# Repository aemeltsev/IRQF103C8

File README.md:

License
-------

IRQF103C8 schematic files and documentations are distributed under 
Creative Commons Attribution 4.0 International License.

Overview
--------
Using STM32 microcontroller for rapid prototyping.

![PCB image][IRQF103C8revC_BRD]

[IRQF103C8revC_BRD]: https://github.com/aemeltsev/IRQF103C8/blob/master/Documents/IRQF103C8revC_BRD.png

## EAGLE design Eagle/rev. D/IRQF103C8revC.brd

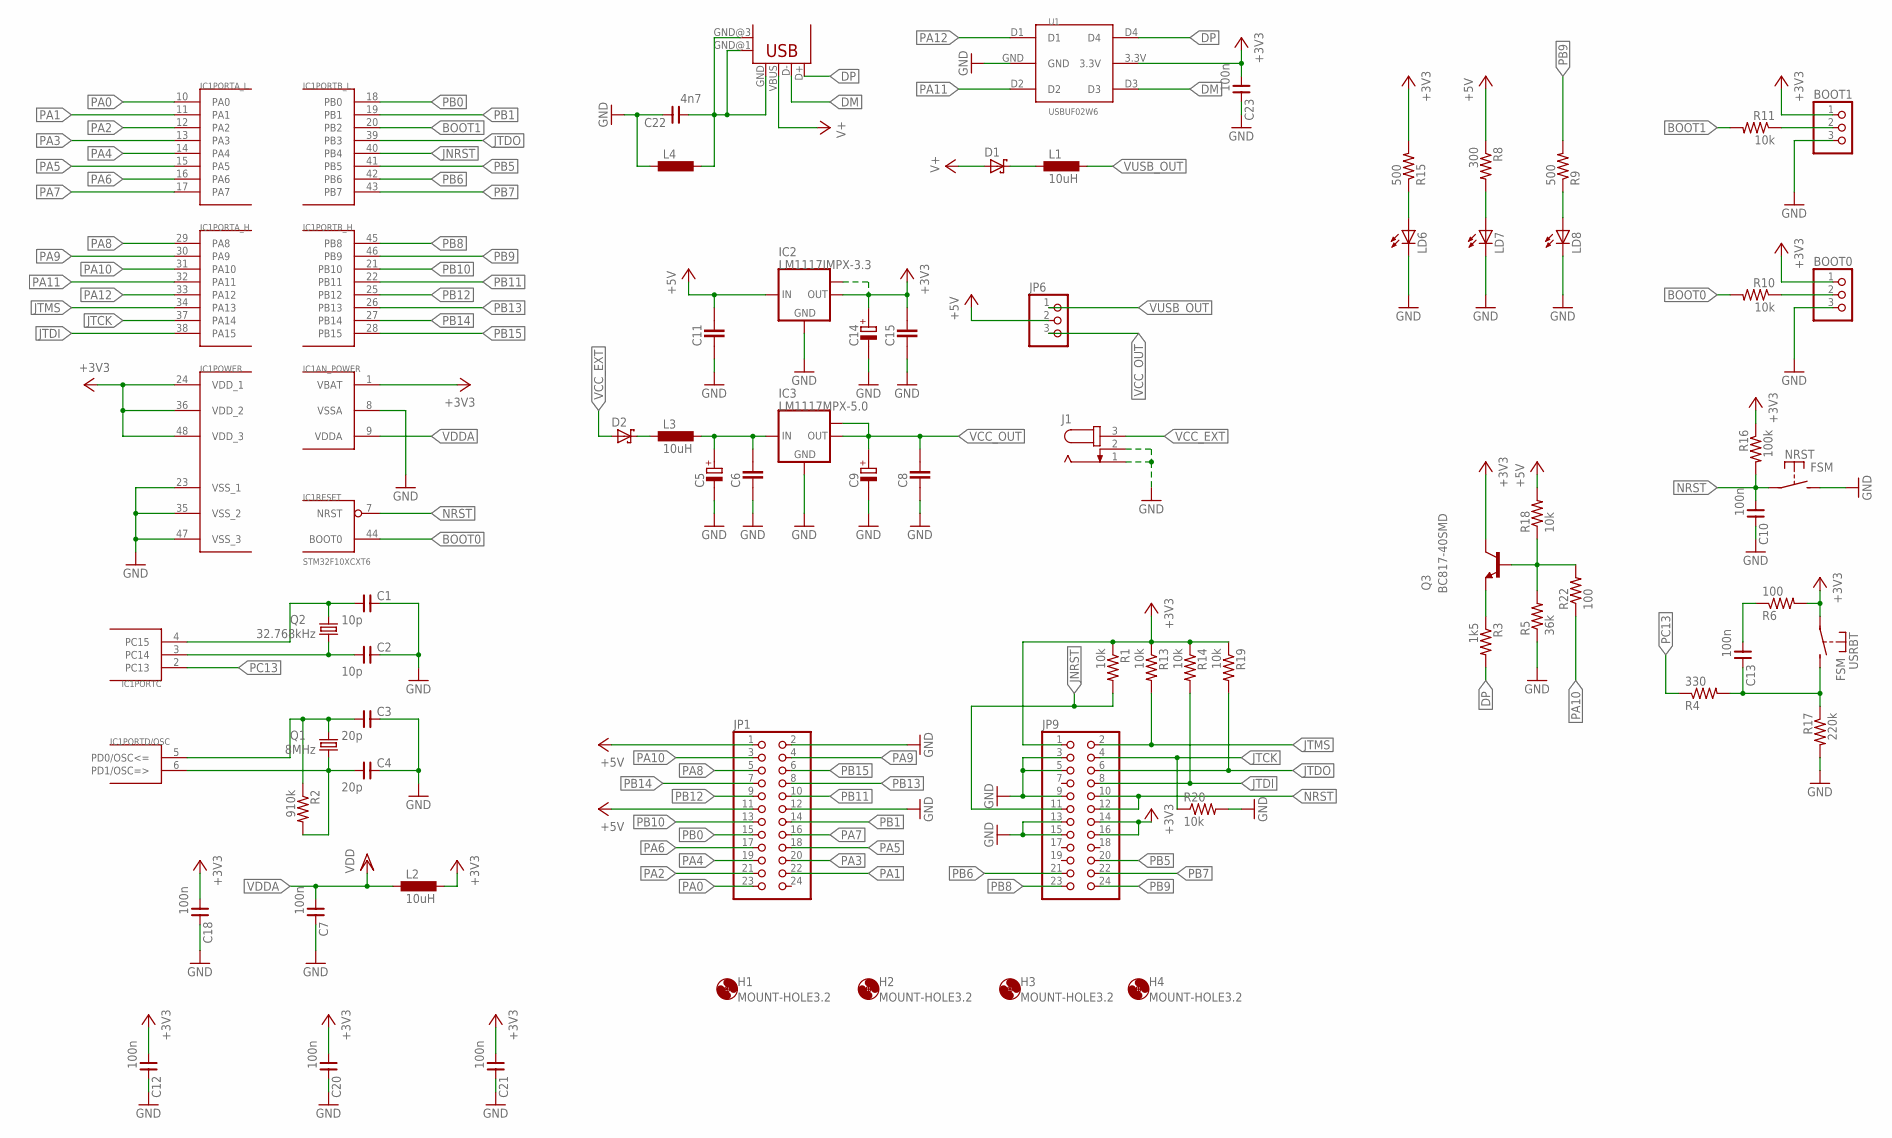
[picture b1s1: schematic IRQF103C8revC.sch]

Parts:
BOOT0, BOOT1: PINHD-1X3; 1X03
C1, C2: 10p; 0805
C3, C4: 20p; 0805
C5: POLARISED_CASE_B; CAPAE430X540N
C6, C8, C15: CAPACITOR_0805; CAPC2012X145AN
C7, C10, C12, C13, C18, C20, C21, C23: 100n; 0805
C9: POLARISED_CASE_D; CAPAE660X540N
C11: CAPACITOR_1206; CAPC3215X168N
C14: POLARISED_CASE_C; CAPAE530X540N
C22: 4n7; 0805
D1, D2: SCHOTTKY_SMA; DIOM5326X292N
H1, H2, H3, H4: MOUNT-HOLE3.2; 3,2
IC1: STM32F10XCXT6; TQFP48
IC2: LM1117IMPX-3.3; SOT223
IC3: LM1117MPX-5.0; SOT223
J1: JACK-PLUG1; SPC4078
JP1, JP9: PINHD-2X12; 2X12
JP6: PINHD-1X3; 1X03
L1, L2, L3: 10uH; INDC1608X95N
L4: INDUCTOR_0603; INDC1608X95N
LD6, LD7, LD8: LEDCHIPLED_0805; CHIPLED_0805
NRST: FSM
Q1: 8MHz; HC49/S
Q2: 32.768kHz; TC26H
Q3: BC817-40SMD; SOT23-BEC
R1, R10, R11, R13, R14, R18, R19, R20: 10k; M0805
R2: 910k; M0805
R3: 1k5; M0805
R4: 330; M0805
R5: 36k; M0805
R6, R22: 100; M0805
R8: 300; M0805
R9, R15: 500; M0805
R16: 100k; M0805
R17: 220k; M0805
U1: USBUF02W6; SOT23-6L
USB1: USB-MB-S
USRBT: FSM

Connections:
+3V3: BOOT0.1, BOOT1.1, C12.1, C14.+, C15.2, C18.1, C20.1, C21.1, C23.1, IC1.1 (VBAT), IC1.24 (VDD_1), IC1.36 (VDD_2), IC1.48 (VDD_3), IC2.2 (OUT), IC2.TAB (OUT1), JP9.1, JP9.14, JP9.16, L2.2, Q3.C, R1.1, R6.2, R13.1, R14.1, R15.2, R16.1, R19.1, U1.3.3V, USRBT.P$1
+5V: C11.2, IC2.3 (IN), JP1.1, JP1.11, JP6.2, R8.1, R18.2
BOOT0: IC1.44 (BOOT0), R10.2
BOOT1: IC1.20 (PB2), R11.2
DM: U1.D3, USB1.D-
DP: R3.2, U1.D4, USB1.D+
GND: BOOT0.3, BOOT1.3, C1.2, C2.2, C3.2, C4.2, C5.-, C6.1, C7.2, C8.1, C9.-, C10.2, C11.1, C12.2, C14.-, C15.1, C18.2, C20.2, C21.2, C22.2, C23.2, IC1.8 (VSSA), IC1.23 (VSS_1), IC1.35 (VSS_2), IC1.47 (VSS_3), IC2.1 (GND), IC3.1 (GND), J1.1, J1.2, JP1.2, JP1.12, JP9.3, JP9.5, JP9.9, JP9.13, JP9.15, L4.1, LD6.C, LD7.C, LD8.C, NRST.P$2 (S), R5.1, R17.2, R20.2, U1.GND
JNRST: IC1.40 (PB4), JP9.11, R1.2
JTCK: IC1.37 (PA14), JP9.4, R20.1
JTDI: IC1.38 (PA15), JP9.8, R14.2
JTDO: IC1.39 (PB3), JP9.6, R19.2
JTMS: IC1.34 (PA13), JP9.2, R13.2
unnamed: C2.1, IC1.3 (PC14), Q2.1
unnamed: C1.1, IC1.4 (PC15), Q2.2
unnamed: C4.1, IC1.6 (PD1/OSC=>), Q1.1, R2.2
unnamed: C3.1, IC1.5 (PD0/OSC<=), Q1.2, R2.1
unnamed: BOOT0.2, R10.1
unnamed: LD7.A, R8.2
unnamed: D2.K, L3.1
unnamed: D1.K, L1.1
unnamed: Q3.B, R5.2, R18.1, R22.2
unnamed: C5.+, C6.2, IC3.3 (IN), L3.2
unnamed: Q3.E, R3.1
unnamed: C13.2, R4.2, R17.1, USRBT.P$2 (S)
unnamed: C13.1, R6.1
unnamed: LD8.A, R9.1
unnamed: C22.1, L4.2, USB1.GND, USB1.GND@1 (GND), USB1.GND@3 (GND)
unnamed: LD6.A, R15.1
NRST: C10.1, IC1.7 (NRST), JP9.10, JP9.12, NRST.P$1, R16.2
PA0: IC1.10 (PA0), JP1.23
PA1: IC1.11 (PA1), JP1.22
PA2: IC1.12 (PA2), JP1.21
PA3: IC1.13 (PA3), JP1.20
PA4: IC1.14 (PA4), JP1.19
PA5: IC1.15 (PA5), JP1.18
PA6: IC1.16 (PA6), JP1.17
PA7: IC1.17 (PA7), JP1.16
PA8: IC1.29 (PA8), JP1.5
PA9: IC1.30 (PA9), JP1.4
PA10: IC1.31 (PA10), JP1.3, R22.1
PA11: IC1.32 (PA11), U1.D2
PA12: IC1.33 (PA12), U1.D1
PB0: IC1.18 (PB0), JP1.15
PB1: IC1.19 (PB1), JP1.14
PB2: BOOT1.2, R11.1
PB5: IC1.41 (PB5), JP9.20
PB6: IC1.42 (PB6), JP9.21
PB7: IC1.43 (PB7), JP9.22
PB8: IC1.45 (PB8), JP9.23
PB9: IC1.46 (PB9), JP9.24, R9.2
PB10: IC1.21 (PB10), JP1.13
PB11: IC1.22 (PB11), JP1.10
PB12: IC1.25 (PB12), JP1.9
PB13: IC1.26 (PB13), JP1.8
PB14: IC1.27 (PB14), JP1.7
PB15: IC1.28 (PB15), JP1.6
PC13: IC1.2 (PC13), R4.1
V+: D1.A, USB1.VBUS
VCC_EXT: D2.A, J1.3
VCC_OUT: C8.2, C9.+, IC3.2 (OUT), IC3.TAB (OUT1), JP6.3
VDDA: C7.1, IC1.9 (VDDA), L2.1
VUSB_OUT: JP6.1, L1.2

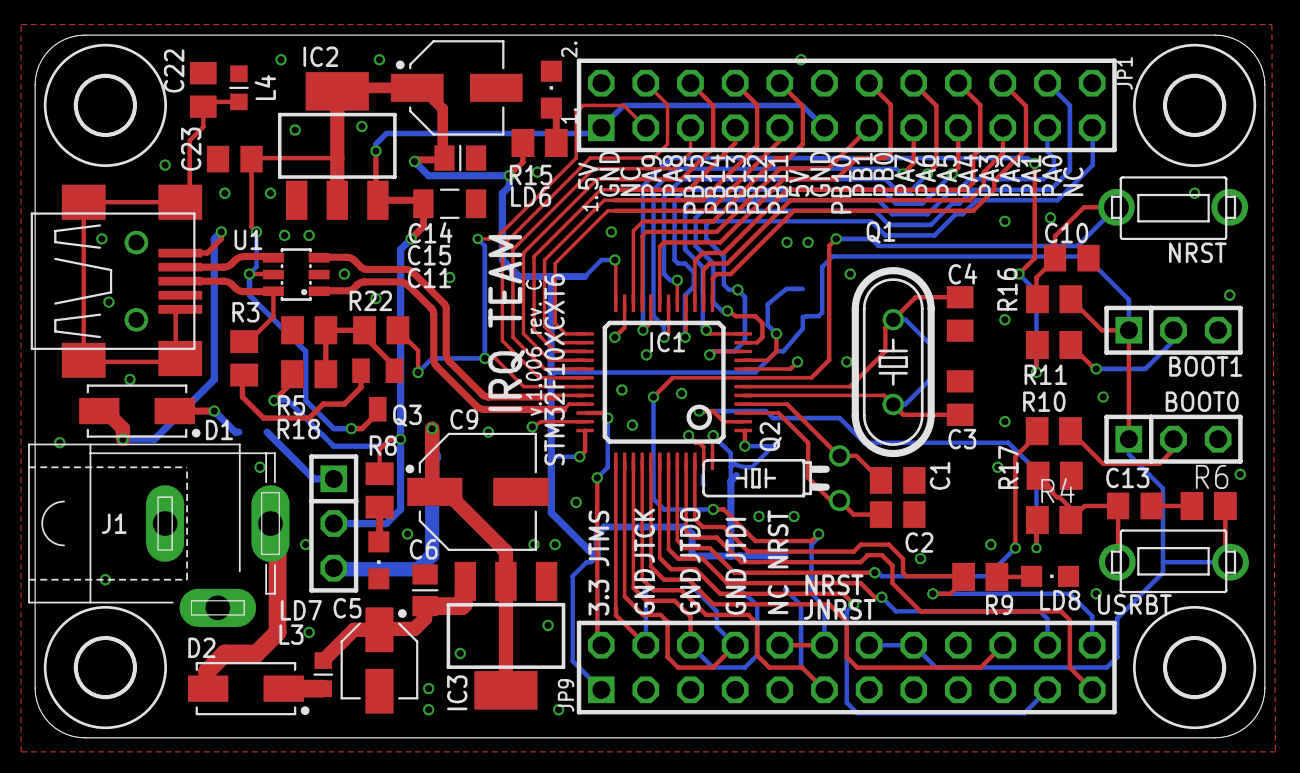
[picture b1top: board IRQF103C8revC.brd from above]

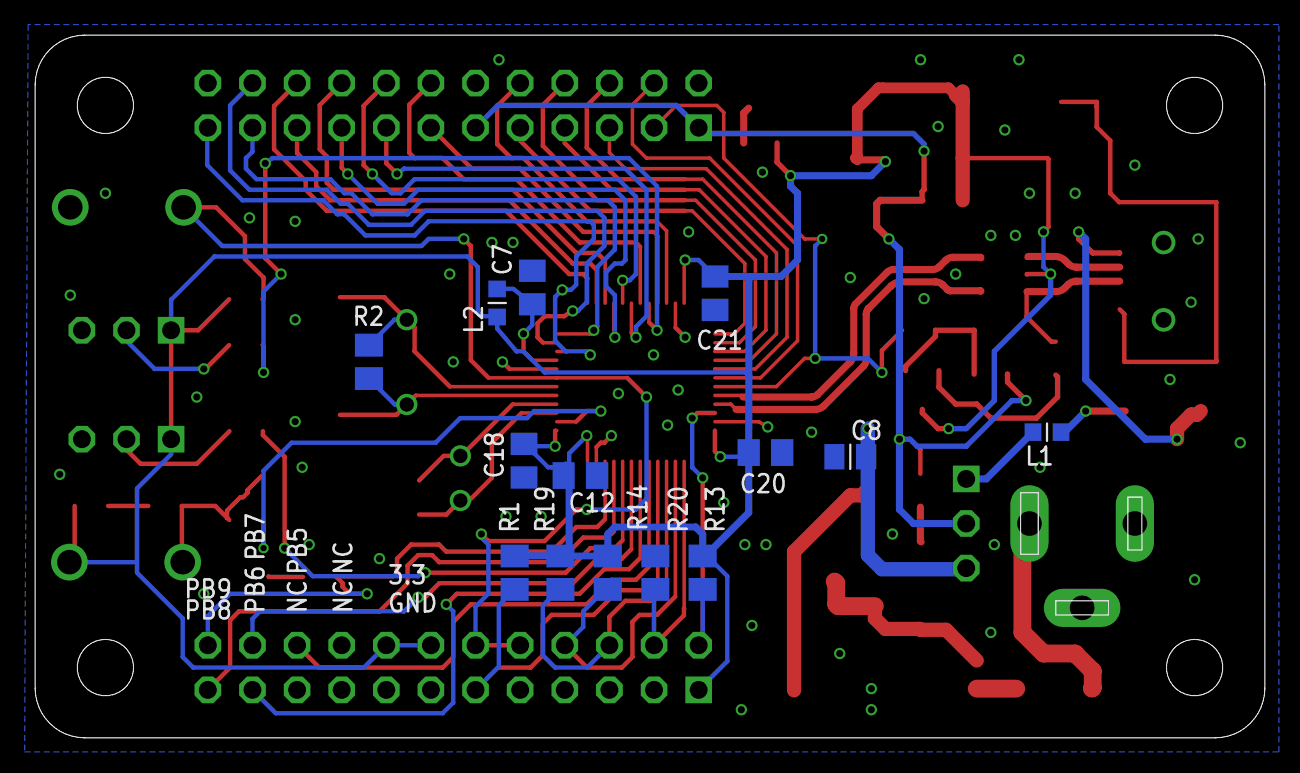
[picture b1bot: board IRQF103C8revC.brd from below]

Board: 2 copper layers, 70.0 x 40.0 mm, 68 parts (14 on the bottom side), 62 nets.

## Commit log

2017-10-15 :boom::camel: Added .gitattributes & .gitignore files
2017-10-15 Add Files
    Add Files
2017-10-16 Add doc dir
    Directory for documents
2017-10-18 Update files
    Update schematic & pcb files
2017-10-26 rev. A
    add revision folder
2017-10-27 refresh
    Refresh and update files
2017-10-31 add readme
    description license & overview
2019-01-10 Rev.C
    Add rev. C, and SCH BRD pdf file
2019-01-10 Update README.md
    Update README.md
2019-01-11 Update README.md
    Add readme image
2020-03-10 rev
    New revision
2020-06-24 update circuit
    Connect GPIOA 10 to NC pin, using pwm
